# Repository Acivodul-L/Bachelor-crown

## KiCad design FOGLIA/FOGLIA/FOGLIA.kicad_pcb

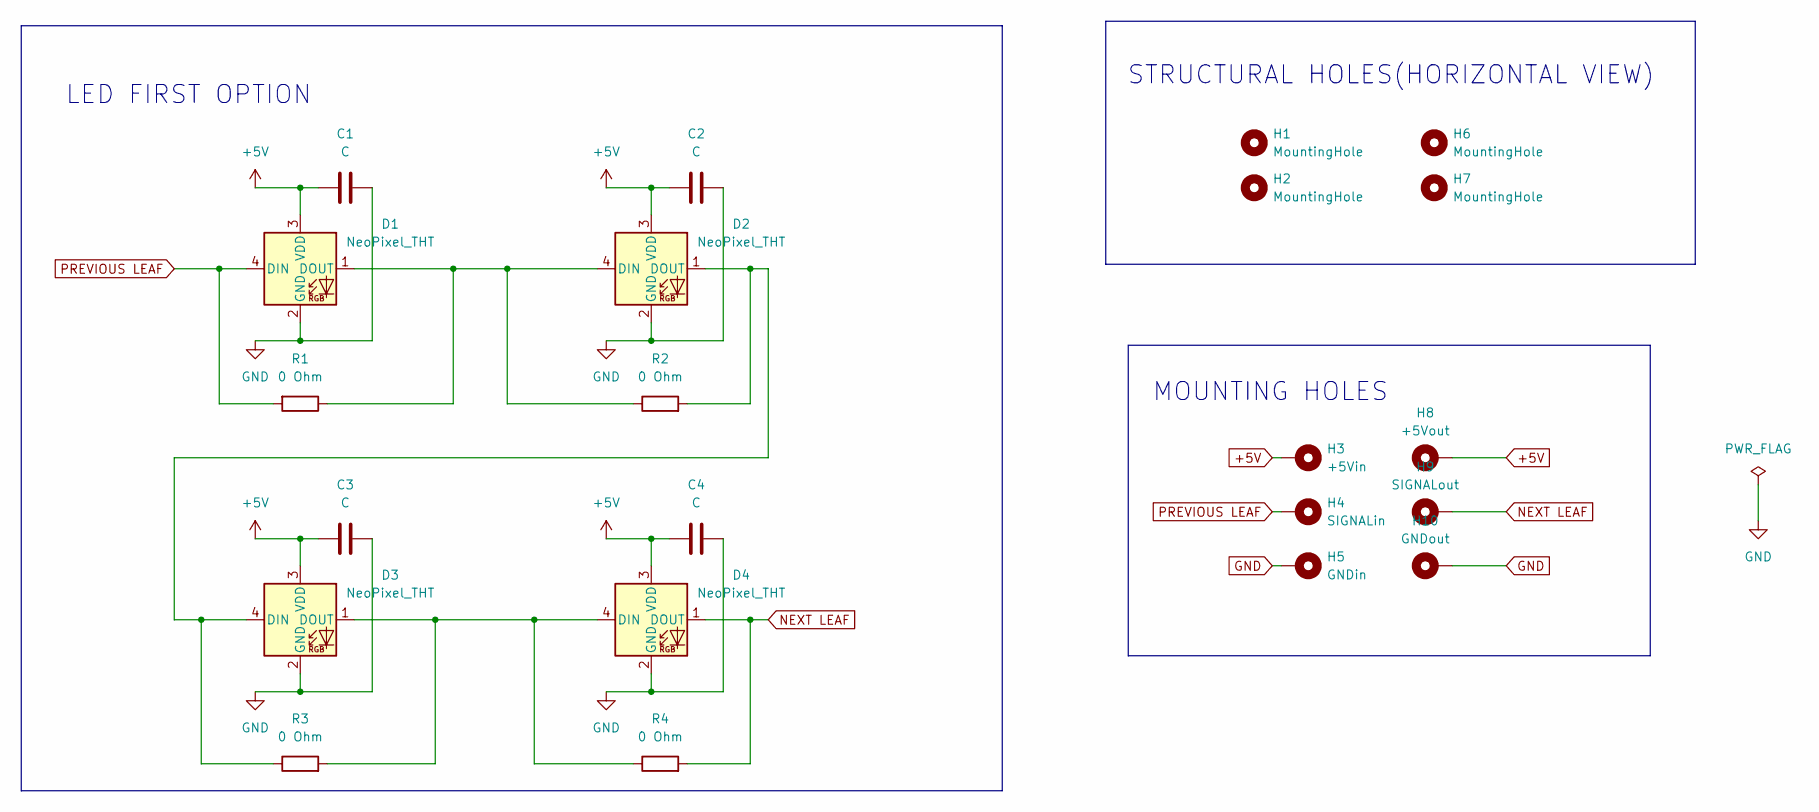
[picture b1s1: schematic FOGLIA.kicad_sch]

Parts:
C1, C2, C3, C4: C; C_0805_2012Metric_Pad1.18x1.45mm_HandSolder
D1, D2, D3, D4: NeoPixel_THT; LED NEOPIXELS CORONA CORRECT
H1, H2, H6, H7: MountingHole; MountingHole_2.1mm
H3: +5Vin; MountingHole_2.2mm_M2_DIN965_Pad
H4: SIGNALin; MountingHole_2.2mm_M2_DIN965_Pad
H5: GNDin; MountingHole_2.2mm_M2_DIN965_Pad
H8: +5Vout; MountingHole_2.2mm_M2_DIN965_Pad
H9: SIGNALout; MountingHole_2.2mm_M2_DIN965_Pad
H10: GNDout; MountingHole_2.2mm_M2_DIN965_Pad
R1, R2, R3, R4: 0 Ohm; R_0805_2012Metric_Pad1.20x1.40mm_HandSolder

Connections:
+5V: C1.1, C2.1, C3.1, C4.1, D1.3 (VDD), D2.3 (VDD), D3.3 (VDD), D4.3 (VDD), H3.1, H8.1
GND: C1.2, C2.2, C3.2, C4.2, D1.2 (GND), D2.2 (GND), D3.2 (GND), D4.2 (GND), H5.1, H10.1
NEXT LEAF: D4.1 (DOUT), H9.1, R4.2
unnamed: D1.1 (DOUT), D2.4 (DIN), R1.1, R2.1
unnamed: D2.1 (DOUT), D3.4 (DIN), R2.2, R3.1
unnamed: D3.1 (DOUT), D4.4 (DIN), R3.2, R4.1
PREVIOUS LEAF: D1.4 (DIN), H4.1, R1.2

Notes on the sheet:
MOUNTING HOLES
STRUCTURAL HOLES(HORIZONTAL VIEW)
LED FIRST OPTION

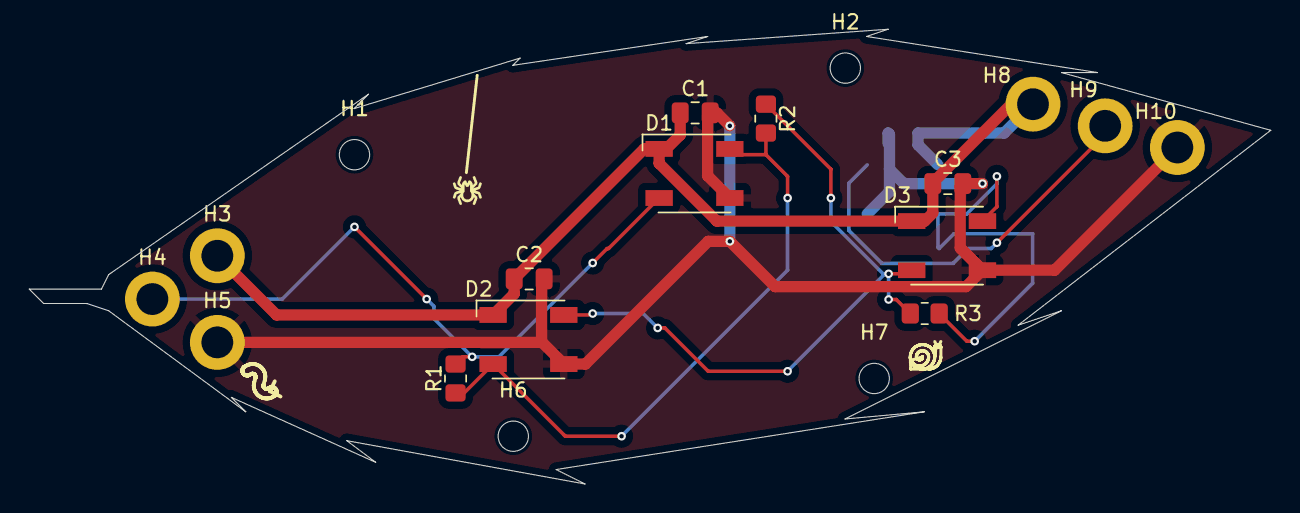
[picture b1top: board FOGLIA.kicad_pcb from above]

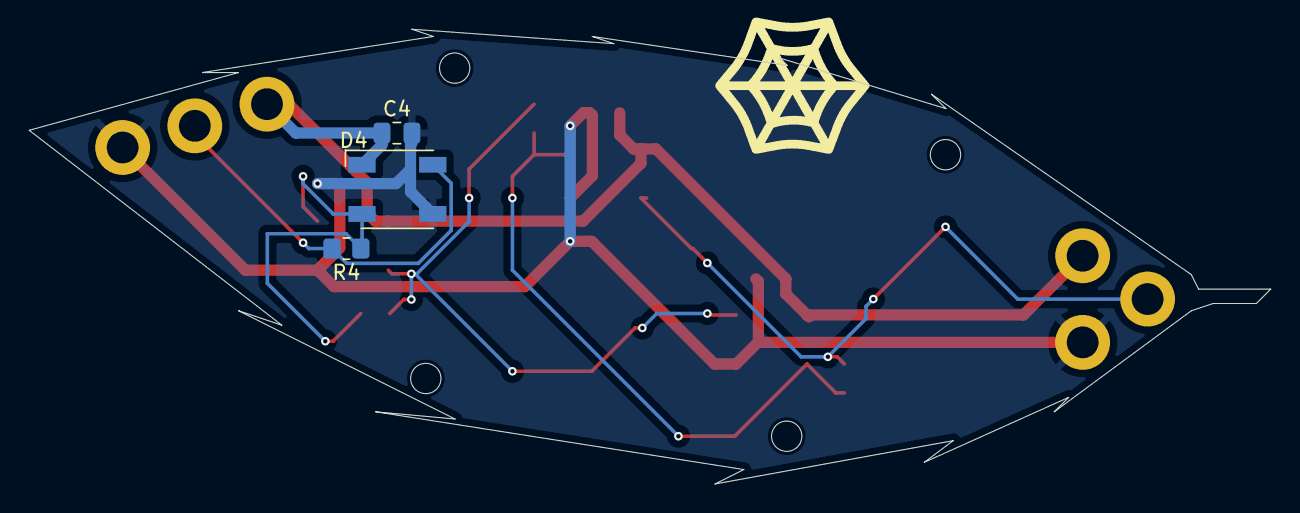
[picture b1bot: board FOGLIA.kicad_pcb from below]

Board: 2 copper layers, 86.0 x 31.5 mm, 22 parts (3 on the bottom side), 7 nets.

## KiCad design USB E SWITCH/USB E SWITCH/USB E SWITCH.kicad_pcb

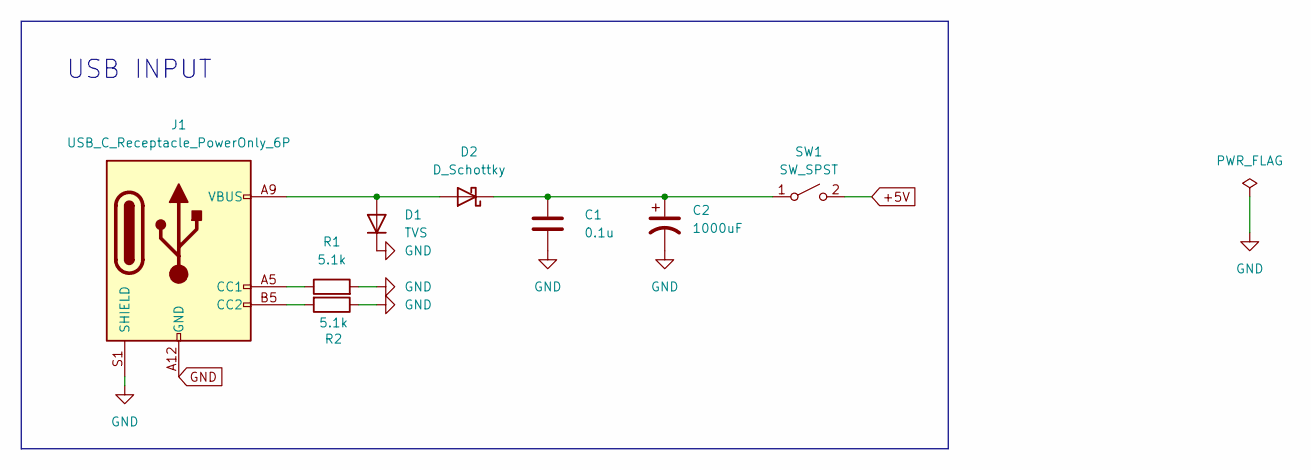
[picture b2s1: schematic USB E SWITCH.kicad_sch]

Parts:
C1: 0.1u; C_0805_2012Metric_Pad1.18x1.45mm_HandSolder
C2: 1000uF; CP_Radial_Tantal_D4.5mm_P2.50mm
D1: TVS; D_0805_2012Metric
D2: D_Schottky; D_0805_2012Metric
J1: USB_C_Receptacle_PowerOnly_6P; USB_C_Receptacle_GCT_USB4125-xx-x-0190_6P_TopMnt_Horizontal
R1, R2: 5.1k; R_0805_2012Metric_Pad1.20x1.40mm_HandSolder
SW1: SW_SPST; switch_corona

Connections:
+5V: SW1.2 (B)
GND: C1.2, C2.2, D1.1 (K), J1.A12 (GND), J1.B12 (GND), J1.S1 (SHIELD), R1.2, R2.1
unnamed: D1.2 (A), D2.2 (A), J1.A9 (VBUS), J1.B9 (VBUS)
unnamed: C1.1, C2.1, D2.1 (K), SW1.1 (A)
unnamed: J1.A5 (CC1), R1.1
unnamed: J1.B5 (CC2), R2.2

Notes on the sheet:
USB INPUT

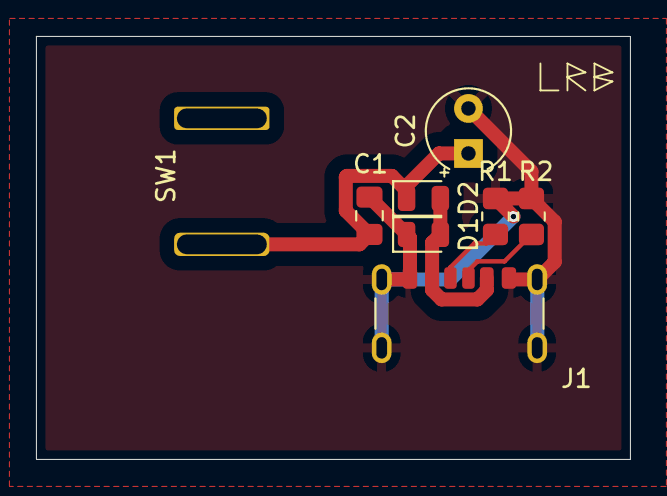
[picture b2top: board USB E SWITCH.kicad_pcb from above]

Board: 2 copper layers, 33.0 x 23.5 mm, 8 parts (0 on the bottom side), 5 nets.

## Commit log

2025-11-26 Caricamento versione locale iniziale
